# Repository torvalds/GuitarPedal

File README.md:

## Resurrected random guitar pedal project

This is a resurrected version of my old guitar pedal project: a digital
guitar pedal built around an RP2354A and a TI audio codec, with all the
effects done in software on a core of its own.

It went through a phase with a little OLED screen and a couple of rotary
encoders on it, and that's gone now.  Editing seventeen effects through a
128x128 screen and two knobs was never going to be pleasant, and I'm not
exactly known for my mad UI designing skillz, so the pedal itself is down
to one knob and one stomp switch and the deep editing happens somewhere
that already has a screen: there's a web app that talks to it over USB
MIDI from a browser.

So what's in here:

 - `Hardware` has the kicad files.
 - `Effects` has the seventeen effects, one file each.  They are up here
   rather than inside the firmware because three different things are
   built from them: the firmware, the test bench, and the web app's
   controls.
 - `Audio` has the DSP the effects are built out of - biquads, envelope
   followers, LFOs - and the audio loop itself.  The bench compiles the
   same files, so what gets measured is the pedal's own arithmetic.
 - `Firmware` is the rest of what runs on the pedal: USB, MIDI, scenes,
   the board pin maps.
 - `WebMIDI` is the web app that edits it.
 - `scripts` is what the build runs - the effect generator, the math
   tables, and the checks that refuse a firmware image doing something
   the audio core shouldn't.
 - `Validation` is the test suite.  Some of it runs on your machine and
   some of it wants a pedal plugged in.
 - `Documentation` remains a very optimistic name for a directory.

## Firmware

I've only ever built the firmware on Linux, but it *should* be perfectly
possible to build on MacOS or Windows too if you just figure out the
platform requirements. The project depends on the `pico-sdk` and
`tinyusb` libraries and on `picotool`, and has submodules for all three, so
they get built automatically, but the build tools your platform has to provide.

Regardless of platform, you'll need the basics:
 - git
 - make
 - python3
 - cmake
 - a C and C++ compiler for the machine you build on, because picotool
   and the SDK's PIO assembler are built from source too
 - pkg-config and the libusb-1.0 development files, for picotool
   (`libusb1-devel` on Fedora, `libusb-1.0-0-dev` on Debian)

and a 32-bit arm cross-build environment.  On Linux, that would be
something like
 - arm-none-eabi-binutils-cs
 - arm-none-eabi-gcc-cs
 - arm-none-eabi-gcc-cs-c++ (the SDK sets up C++ as well as C)
 - arm-none-eabi-newlib

On Fedora that whole list is

    dnf install git make python3 cmake gcc-c++ pkgconf-pkg-config \
        libusb1-devel arm-none-eabi-gcc-cs arm-none-eabi-gcc-cs-c++ \
        arm-none-eabi-newlib

The `ble` board also carries the nRF54 radio's firmware, which is a
Zephyr build of its own.  ``make -C nRF54 fetch`` sets that up once: a
python venv with west in it, the Nordic SDK, and Zephyr's ARM toolchain
in `~/zephyr-sdk-*`, about 7.5GB between them.  It also needs ninja
(`ninja-build` on Fedora).

There's more than one board this can be built for, and the build won't
guess.  You say which one this tree is about once, in
`board.local`, and it stays said - it's a file rather than a
cmake cache variable specifically so that blowing away `build/` doesn't
silently change your mind for you.  So:
```
	git clone https://github.com/torvalds/GuitarPedal.git
	cd GuitarPedal
	echo unified > board.local
	make prep
	make
```
`unified` is the current one-board pedal.  The other is `split`, which is
the older modular pair of boards.  If you forget this step the configure
will stop and tell you, which is the intended behaviour - a wrong board
should be an error you fix once, not a working build for hardware you
don't have.

That gets you `build/pedal-unified.uf2` (and `.elf`, and `.bin`).  Every
artifact is named for the board it's for, so there is deliberately no
`pedal.uf2` to grab by mistake.  You can build the other board without
changing what the tree is about - ``make split`` - or both with ``make
all-boards``.

To get the `.uf2` onto the pedal you need it in BOOTSEL mode, and there
are two ways.  If it's running and plugged in, send it MIDI CC 20 with
value 126 and it will reboot into BOOTSEL on its own:
```
	amidi -l                          # find which card the pedal is
	amidi -p hw:5,0 -S "B0 14 7E"     # ...and that 5 is mine, not yours
```
Otherwise, hold the knob in while you plug it in.  The rotary encoder's
switch doubles as BOOTSEL on this board - through a Schottky, so that
QSPI traffic can't fake pulling it low - and that's the route that still
works on a pedal too broken to enumerate.  The older boards had a proper
BOOTSEL button, but it was on the little MCU daughtercard, which is fine
on a bench and useless the moment the thing is screwed into a box.

Either way a USB mass storage device shows up and you copy the file to
it.

The build makes its own picotool, with USB support, so you can also skip
all that and just do ``make flash``, which builds and flashes the board in
`board.local`.
``make flash-split`` does the other one.

### Tools outside the tree

Two tools stay outside the tree, and each has a make target that
sets it up once per machine.  Both say what they are missing, and
running either again is safe.

``make probe-rs`` builds probe-rs, which programs and debugs the nRF54
radio through the pedal, from `~/src/probe-rs` into `~/bin/probe-rs`.
It needs cargo and the libudev development files (`systemd-devel` on
Fedora).

``make build123d`` makes a python venv in `~/.build123d` for the
3D-printed case in `Hardware/Models`, and two commands in `~/bin` that
use it: ``build123d Compact.py`` runs the model, and ``ocp-viewer`` is
the viewer it draws in, at http://localhost:3939.

### Talking to the pedal without root

picotool and probe-rs open the pedal's USB device directly, and without
a udev rule only root can.  This is `/etc/udev/rules.d/99-pedal.rules`:

    ATTR{idVendor}=="2e8a", MODE="0660", GROUP="dialout"
    ATTR{idVendor}=="ffff", ATTR{idProduct}=="0003", MODE="0660", GROUP="dialout"

The first line covers anything with Raspberry Pi's vendor id, which is
how a board in BOOTSEL shows up; the second is the running pedal, whose
CMSIS-DAP interface is what probe-rs uses for the radio.  You have to be
in the `dialout` group, and ``udevadm control --reload`` as root plus a
replug picks the rule up.  USB audio and MIDI need no rule.

The pedal's debug console is `/dev/ttyACM0`, which needs a kernel with
`CONFIG_USB_ACM`.  Every distribution kernel has it; a kernel you
configured yourself may not.

### Testing

`Validation` has the test suite, and it's split by what it needs.

``make check`` needs gcc and numpy (`python3-numpy`), plus node if
you want the web app's tests too; without node those are skipped.  The
bench scripts that talk to a pedal want more: alsa-utils, ffmpeg, scipy
and matplotlib, ngspice for the circuit comparisons, and dbus-python and
PyGObject for Bluetooth MIDI.  On Fedora,

    dnf install python3-numpy nodejs alsa-utils ffmpeg-free psmisc \
        python3-scipy python3-matplotlib ngspice python3-dbus python3-gobject

``make check`` runs the part that needs no hardware at all: the MIDI
packetiser, whether the web app still loads and still draws the right
conclusions, and a sweep that asks every biquad in the pedal where it
actually landed.  ``make check-biquad`` is that last one on its own, and
``make check-effects`` puts signals through the effects themselves.

That last one works because of `Validation/bench`, which builds the
pedal's actual audio core - the same `single_sample()`, the same effect
headers, the same compiler flags - as a program on your machine that
takes float samples on stdin and hands them back on stdout.  It is not a
model of the signal path.  It's the signal path, with the two register
blocks the audio core touches replaced by ordinary memory.

``make check-analysis`` is the other host-only one, and it is what keeps
the per-effect pages under `Documentation/effects` honest: every curve on
those pages is a measurement, and this re-measures and says when one has
stopped being true.  It is separate from ``check`` because it re-runs
every sweep on every page, which is slow.

Then there are the ones that want hardware: ``make check-hw`` with a
signal generator, ``make check-analog`` with a patch cable from the
pedal's output back to its own input, ``make check-bench`` to ask whether
a real board agrees with the host build, ``make check-hwtone`` to sweep
the tone stack the codec runs in its own biquads, and ``make check-loop``
if you have two pedals to patch into each other.

### Checking generated metadata

After generating metadata, check existing outputs without changing them:

```sh
python3 scripts/gen_effects.py --check Effects/ build/effect_map.h WebMIDI/effects.js Documentation/MIDI_CC_MAP.md
```

Use the output paths from your build if they differ. This checks the three
named files and `midi_schema.h` beside the C header. Exit status is 0 when
current, 1 for missing or stale output, and 2 for an input or I/O error.
Missing/stale files are listed with a regeneration command. Ordinary
generation without `--check` remains the way to create or refresh them.
Run the hardware-free regression tests with
`make -C Validation test-generated-metadata`; they also run under
`make -C Validation check`.

## Hardware

The kicad design files (and some supporting infrastructure, like the 3D
printed insert and the enclosure drill rules) are in the ``Hardware``
subdirectory.

These days it's just the one board.  `Hardware/usb-stomp` has the RP2354A
and the TI TAC5242 codec sitting directly on it, and that's the whole
pedal: no cable, no daughtercards, no connectors in between.

What's on it:

 - a 1/4" input jack and a 1/4" output jack
 - a third 1/4" jack for an expression pedal or a remote stomp switch
 - MIDI in and out, on 3.5mm "Type A" TRS jacks (out through a 5V
   buffer, in through an optocoupler, like MIDI has always wanted)
 - USB-C, and the usual 9V guitar pedal power jack
 - one rotary encoder with a switch under it, and one stomp switch
 - three addressable WS2812B LEDs

The MIDI jacks and the expression jack are the genuinely new things.  The
older boards had nowhere to put them - the expression jack in particular
wants two ADC pins, and those are exactly the pins the old MCU board was
spending on hardware MIDI, so it could not have existed there at all.

Fair warning on that expression jack, though: the hardware is done and
the firmware can read it, but only when the host asks it to over SysEx.
Right now it's a probe for figuring out what people actually plug in
there - expression pedals don't even agree on which contact is the wiper
- and nothing is wired up to *do* anything with the result yet.

### How it used to be

It used to be modular, and those board files are all still here.  There
were two little daughtercards for the "core" hardware - the RP2354
microcontroller (`Hardware/rp2354`) and the TI TAC5112 codec
(`Hardware/codec`) - plus a board for the audio and 9V DC power jacks
(`Hardware/audio-jacks`), and a main board (`Hardware/pedal-board`) for
the pedal IO: i2c connector for the screen, USB-C programming port,
rotary encoders, pin header for stomp switches.  The two halves were
joined by a 12P 0.5mm FFC cable carrying power and data lines (i2c for
control, i2s for audio).

That was mostly so I could try out different form factors.  It let me lay
the two halves out independently, and it was flexible enough to cram a
125B enclosure full of jacks, rotaries and the screen all in one top
area.  There was also a worry about noise isolation, which in the end
never had to be tested.

I used the nice HiRose BM28 series connectors on the modular boards.
They are absolutely tiny, which makes for a great board footprint but
admittedly also makes for a slightly more complicated board due to the
tiny 0.35mm pitch.  I'm not a fan of the traditional pin headers simply
because they make it so hard to do compact form factors.

Those boards are finished and they still work - the firmware builds for
them, and they're still useful for testing.  But what this section used
to say was that if you know what you want, you should just put the codec
directly on the audio jack board and the rp2354 on the IO board.  Which,
yes.  That's the board above.

### Images

The bare `usb-stomp` board, powered up.

## Basic UI

There's no screen.  The pedal has one knob, one footswitch and three
LEDs, and everything else happens in a browser.

### On the pedal

Out of the box the footswitch is bypass - tap for in-circuit or not, hold
it for the tuner - and the knob is the master volume, with either kind of
press on it putting the volume back where it started.  That last one
sounds trivial and isn't: it's the way back when you can't see anything.

But none of that is compiled in.  There are five gestures - turn the
knob, tap it, hold it, tap the switch, hold the switch - and what each
one means is a table the pedal looks up and the app writes.  You can
point the knob at any parameter of any effect, or make a single press
take one effect's mix up while it takes another's down.  A pedal with no
screen can't tell you what its knob is for, so that has to be settable
from something that can.

The three LEDs, left to right: something is wrong (red for clipping,
amber for dropped samples), in circuit or bypassed, and the chain is
busy - where "busy" means whatever the effect thinks it means, so the
gate lights it while it's gating and the compressor while it's
compressing.

### In the browser

`WebMIDI` is a static web page that talks to the pedal over USB
MIDI.  There's nothing to install and it runs off a phone.

It also talks to the pedal over Bluetooth MIDI.  On Linux, Chrome only
offers Bluetooth to a page with
`chrome://flags/#enable-experimental-web-platform-features` turned on;
USB needs nothing.

It doesn't know what the effects are.  It asks.  The pedal describes
every effect it has - every pot, the ranges, the units, the hover text -
and the app builds itself out of that, so it can't drift out of step with
the firmware, and adding an effect to the pedal makes it show up in the
app without touching the app.

What you actually do there is *route*.  There are seventeen effects and
none of them are in your signal path until you say so: routing picks
which ones run, and in what order, and the order is yours, because a
boost in front of a delay is a different pedal from a delay in front of a
boost.  Whatever you don't route costs nothing.

Pots are mostly just numbers, except where they aren't - the tone stacks,
the parametric EQ and the cab sim draw their actual frequency response,
so you can see the curve instead of inferring it from three knob
positions.

A tone stack with a 10dB mid bump at 810Hz and a tape echo behind it, and
the fifteen effects that aren't routed sitting at the bottom waiting to
be.  The faint grey line is the phase response.

Eight scenes fit in the pedal's own flash.  A scene is a routing plus
everything set inside it, and a MIDI program change recalls one, which is
half of what those MIDI jacks are for: a cheap footswitch can step
between scenes with no computer in sight.

## Audio effects

Nineteen of them, plus five that are always there and can't be
unrouted: the **Signal Chain** at the front, which is the input trim, the
noise gate and the master volume
([measured](Documentation/effects/signal-chain.md)), and behind them the
**Settings**, which is whether the input jack is carrying one channel or
two, the MIDI channel, LED brightness and what the tuner is tuning to,
the **USB Audio**, which is what crosses the wire in each direction, the
**Bluetooth Audio**, which is where audio from a phone joins, how loud it
is and what goes back, on a board with a radio, and the **Expression Jack**, which is what
is plugged into it and where that thing's travel ends.

They're listed in the order they run in by default.  This is an overview
and not documentation - the app is the reference, because it gets the
ranges, the units and the hover text from the pedal itself rather than
from anything I typed here.

 - **Hum Filter** - removes the hum single coils and noisy power put on
   the guitar, cutting only the hum's own frequencies, so a clean supply
   gets no cuts at all.  Switching it on the first time, or moving the
   target, listens for a few seconds with the sound left on, so you hear
   the hum go: keep the strings quiet while it does.  It runs ahead of
   the noise gate.  It does not reach the high buzz some USB chargers
   add, and a power bank is quieter there anyway.
 - **Tone** - bass, mid and treble, with the corner frequencies
   adjustable and the mid's Q as well.  There are two of them, so one
   can go in front of a distortion and one behind it.
 - **Analog In Tone** and **Analog Out Tone** - the same three bands
   again, running in the codec's own biquads rather than in the chain.
   They cost the audio core nothing, and they keep the two channels
   apart where Tone folds them together.  Routed like anything
   else, but drawn at the ends of the chain because that is where they
   are: analog is the operative word, and they sit outside everything
   USB audio can reach, so a Dry capture has already been through the
   input one and a Wet capture has not yet been through the output one.
   They need a board whose codec answers on i2c.
 - **Preamp** - a two-stage 12AX7 model, class-A biased with the
   asymmetry left in, and a JFET stage after it.
 - **Compressor** - level, ratio, attack, release, and a boost, so it
   can also just be a clean boost when that's what you want.  The
   threshold reaches low enough to work on a quiet pickup with nothing
   in front of it.  [Measured](Documentation/effects/compressor.md).
 - **Auto-Wah** - an envelope filter that sweeps a resonant filter with
   the guitar's pick dynamics, by Jacky Mpoka.  Lowpass mode preserves low-end body while
   sweeping harmonics (Mu-Tron III style); Bandpass mode isolates the
   resonant peak for classic vocal wah (Crybaby style).  Sweeps up for
   funk quack or down for synth sweeps.
 - **Boost**, with distortion.  I like this one.  Others may not.  Set
   the boost stupidly high and the level low, and instead of clipping at
   the level the signal *folds* back down, which gives you harmonics
   that a soft or hard clipper doesn't.
 - **Klonlike** - the obvious model: 18V charge pump for headroom,
   germanium diodes, and the clean/dirty blend that tracks the gain
   knob.  Originally by Bryan Leavelle.
   [Measured](Documentation/effects/klon.md).
 - **Rat Sketch** - a ProCo RAT, from the Aion FX Helios clone.  One
   op-amp with up to 67dB and several decibels an octave of treble
   emphasis inside the feedback, then diodes to ground, then the one
   backwards Filter knob.  Three clipping modes, because the pedal has
   three.  The op-amp saturates inside its own loop and the diodes are
   solved rather than approximated, which is where its second harmonic
   comes from.  [Measured](Documentation/effects/rat.md).
 - **Phaser**, **Flanger** and **Vibrato** - the modulation three.  All
   simple, all a delay line and an LFO wearing different hats.
 - **Tape Echo** - the Echo King from Cleveland Music Co, a model of the
   Maestro Echoplex tape delays, converted from the Hothouse examples.
   All credit to Ricky Sheaves, and blame me for the conversion.
 - **Reverb** - comb filters into allpasses, the traditional way.
   [Measured](Documentation/effects/reverb.md).
 - **Pitch** - not the clever FFT kind.  It walks a delay line faster or
   slower than real time in two phases, crossfaded with a sine so the
   wrap doesn't click.  So it shifts *and* delays, and it feeds back into
   itself, which makes it a short echo that shifts again on every repeat.
   Most natural an octave up, but it does fractions.
 - **Tremolo** - amplitude modulation, several shapes.
 - **Parametric EQ** - five bands, two shelves and three peaks, every one
   of them tunable across the whole range.
 - **Frenchie Amp** - a small amp: triode, tone stack, power amp.
 - **Test Tone** - sine, triangle, saw or noise at a known level and
   frequency.  It replaces the input rather than adding to it, which is
   what lets the pedal measure itself.
 - **Cabinet** - a speaker cone as a moving mass rather than as a filter,
   integrated at the sample rate.  Pick one of five cabinets and it knows
   the rest of itself; the knobs are how hard the amp drives it, how much
   the amp lets its resonance bloom, and where the mic is pointed.

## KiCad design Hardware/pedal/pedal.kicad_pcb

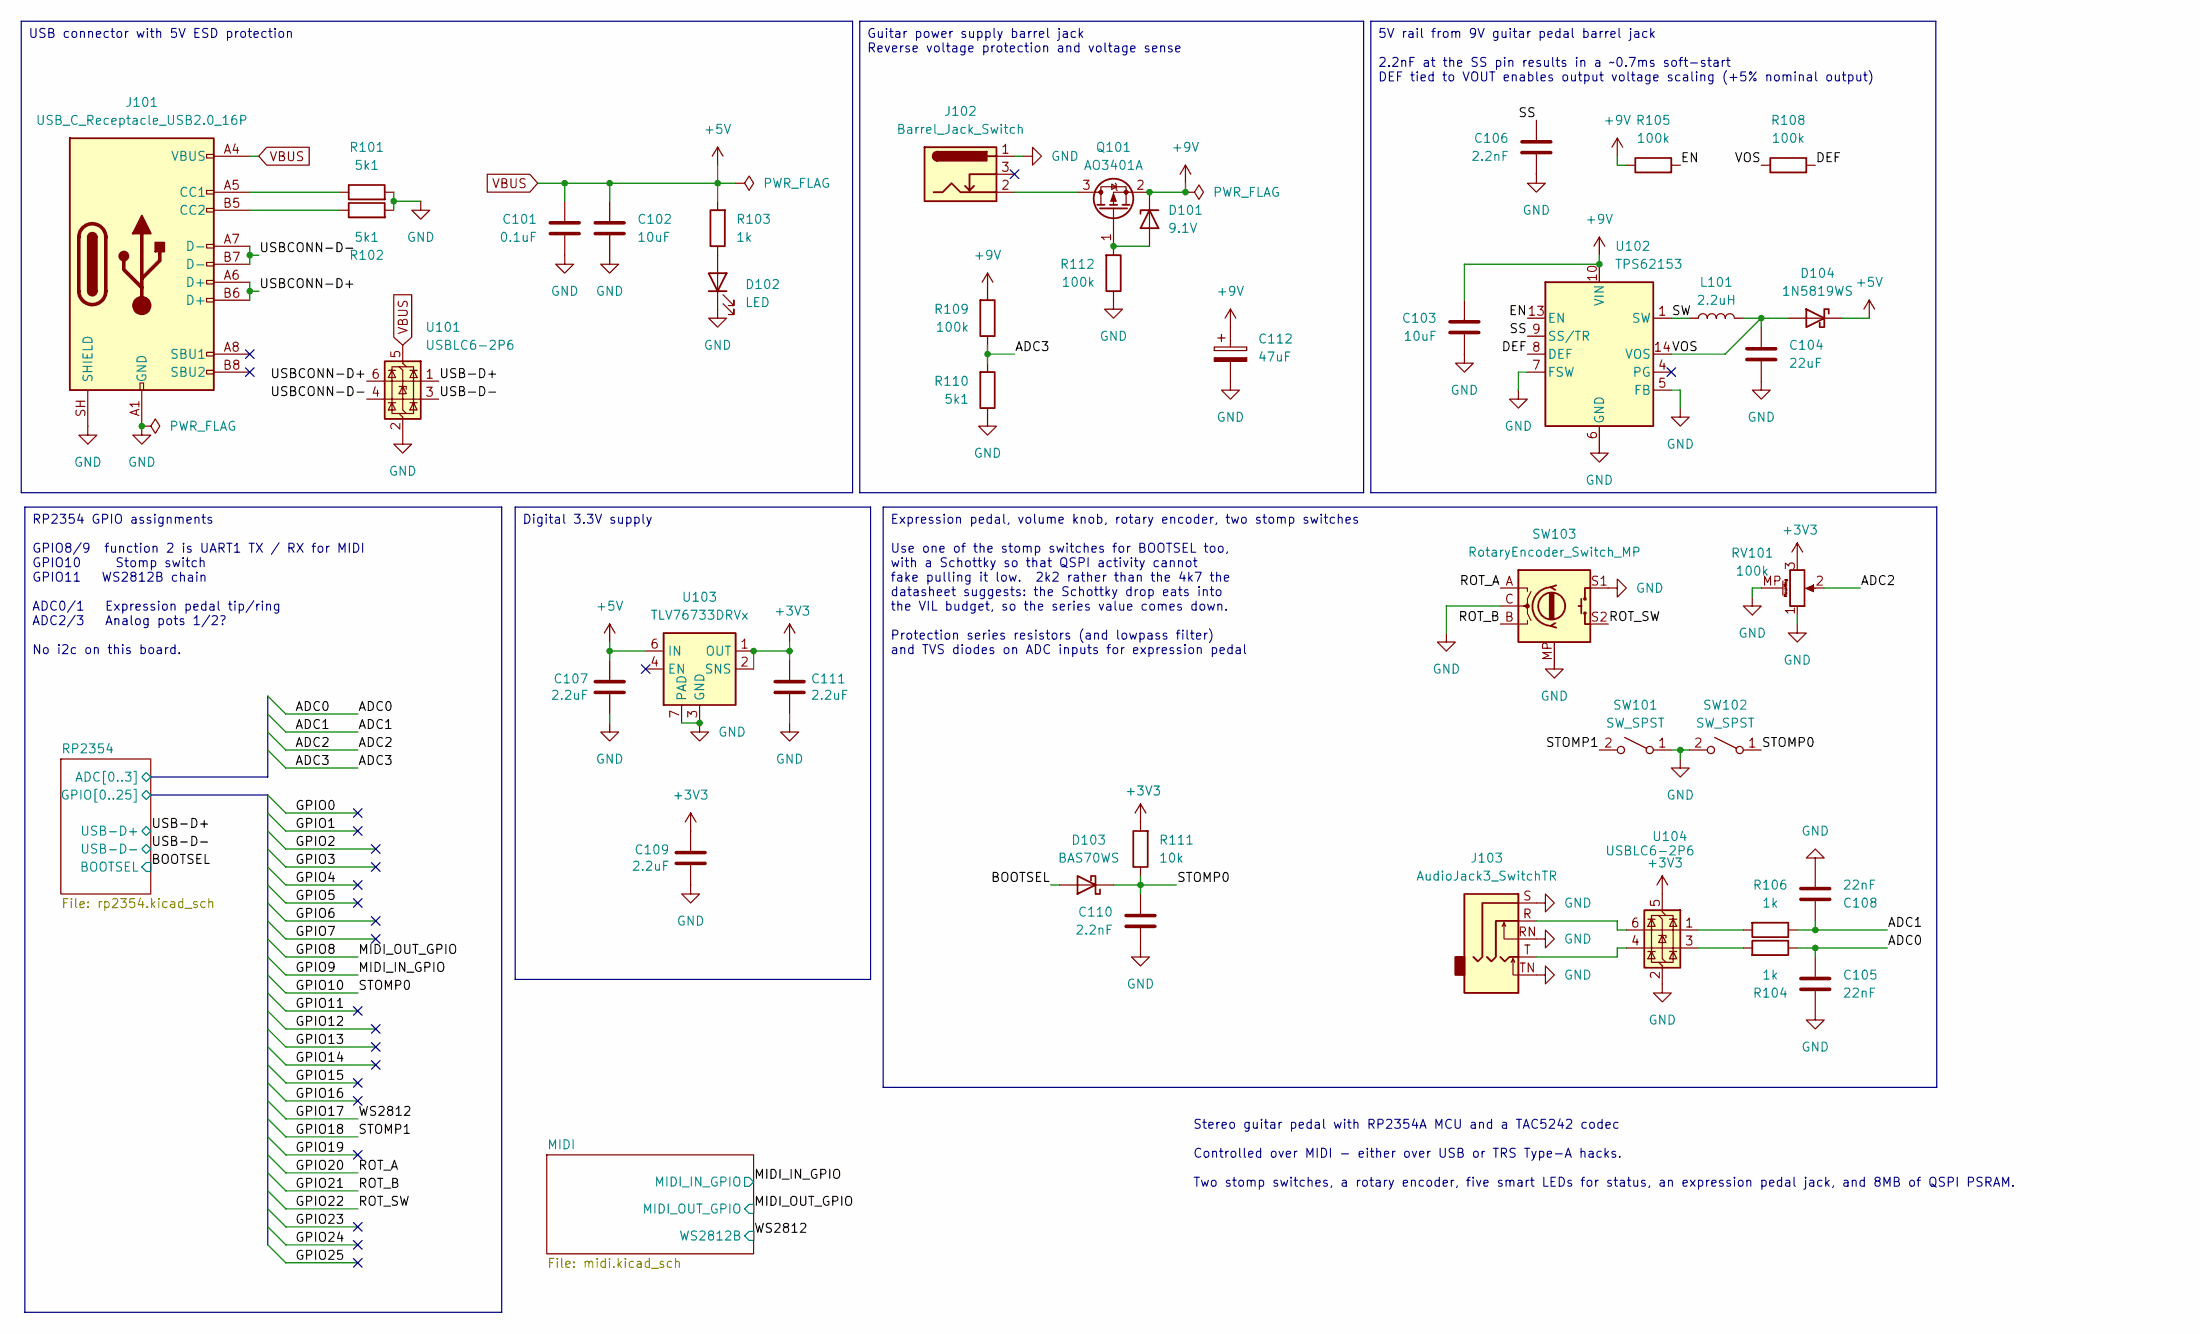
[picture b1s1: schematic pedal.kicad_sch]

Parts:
C101: 0.1uF; C_0402_1005Metric; MANUFACTURER_PART_NUMBER CL05B104KO5NNNC; LCSC PN C1525
C102, C103: 10uF; C_0603_1608Metric; MANUFACTURER_PART_NUMBER GRM188R61E106MA73D; LCSC PN C91606
C104: 22uF; C_1210_3225Metric; MANUFACTURER_PART_NUMBER CL32B226KAJNNNE; LCSC PN C309062
C105, C108: 22nF; C_0402_1005Metric; MANUFACTURER_PART_NUMBER 0402B223K500NT; LCSC PN C1532
C106, C110: 2.2nF; C_0402_1005Metric; MANUFACTURER_PART_NUMBER GRM1555C1H222GA01D; LCSC PN C2987940
C107, C109, C111: 2.2uF; C_0603_1608Metric; MANUFACTURER_PART_NUMBER GRM188Z71E225KE43D; LCSC PN C415535
C112: 47uF; CP_Elec_6.3x5.9; MANUFACTURER_PART_NUMBER EEHZA1V470P; LCSC PN C178639
D101: 9.1V; D_SOD-323; MANUFACTURER_PART_NUMBER BZT52C9V1S; LCSC PN C19077445
D102: LED; LED_0402_1005Metric; MANUFACTURER_PART_NUMBER LTST-C281KGKT; LCSC PN C160479
D103: BAS70WS; D_SOD-323; MANUFACTURER_PART_NUMBER BAS70WS; LCSC PN C7502716
D104: 1N5819WS; D_SOD-323; MANUFACTURER_PART_NUMBER 1N5819WS; LCSC PN C191023
J101: USB_C_Receptacle_USB2.0_16P; USB_C_Receptacle_GCT_USB4105-xx-A_16P_TopMnt_Horizontal; MANUFACTURER_PART_NUMBER GT-USB-7010C; LCSC PN C2843967
J102: Barrel_Jack_Switch; Wurth WR-DC 2.1mm Power Jack
J103: AudioJack3_SwitchTR; NRJ6HM-1-PRE
L101: 2.2uH; L_0806; MANUFACTURER_PART_NUMBER DFE201612E-2R2M=P2; LCSC PN C337893
Q101: AO3401A; SOT-23; MANUFACTURER_PART_NUMBER AO3401A; LCSC PN C15127
R101, R102, R110: 5k1; R_0402_1005Metric; MANUFACTURER_PART_NUMBER 0402WGF5101TCE; LCSC PN C25905
R103, R104, R106: 1k; R_0402_1005Metric; MANUFACTURER_PART_NUMBER RT0402FRE071KL; LCSC PN C136974
R105, R108, R109, R112: 100k; R_0402_1005Metric; MANUFACTURER_PART_NUMBER 0402WGF1003TCE; LCSC PN C25741
R111: 10k; R_0402_1005Metric; MANUFACTURER_PART_NUMBER 0402WGF1002TCE; LCSC PN C25744
RV101: 100k; Potentiometer_9mm_MP_Low_profile
SW101, SW102: SW_SPST; Daier PBS-24B-4
SW103: RotaryEncoder_Switch_MP; RotaryEncoder_EC11-Switch_Vertical_H20mm
U101, U104: USBLC6-2P6; SOT-666; MANUFACTURER_PART_NUMBER USBLC6-2P6; LCSC PN C15999
U102: TPS62153; VQFN-16-1EP_3x3mm_P0.5mm_EP1.68x1.68mm_ThermalVias; MANUFACTURER_PART_NUMBER TPS62153RGTR; LCSC PN C477927
U103: TLV76733DRVx; WSON-6-1EP_2x2mm_P0.65mm_EP1x1.6mm; MANUFACTURER_PART_NUMBER TLV76733DRVR; LCSC PN C2848334

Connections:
+3V3: C109.1, C111.1, R111.2, RV101.3, U103.1 (OUT), U103.2 (SNS), U104.5 (VBUS); also elsewhere on the board
+9V: C103.1, C112.1, D101.1 (K), Q101.2 (S), R105.1, R109.2, U102.10 (VIN), U102.11 (VIN), U102.12 (VIN)
/BOOTSEL: D103.2 (A); also elsewhere on the board
/DEF: R108.2, U102.8 (DEF)
/EN: R105.2, U102.13 (EN)
/RP2354/ADC0: C105.1, R104.1; also elsewhere on the board
/RP2354/ADC1: C108.1, R106.1; also elsewhere on the board
/RP2354/ADC2: RV101.2; also elsewhere on the board
/RP2354/ADC3: R109.1, R110.2; also elsewhere on the board
/RP2354/GPIO10: C110.2, D103.1 (K), R111.1, SW102.1 (A); also elsewhere on the board
/RP2354/GPIO18: SW101.2 (B); also elsewhere on the board
/RP2354/GPIO20: SW103.A; also elsewhere on the board
/RP2354/GPIO21: SW103.B; also elsewhere on the board
/RP2354/GPIO22: SW103.S2; also elsewhere on the board
/SS: C106.2, U102.9 (SS/TR)
/SW: L101.1, U102.1 (SW), U102.2 (SW), U102.3 (SW)
/USB-D+: U101.1 (I/O1); also elsewhere on the board
/USB-D-: U101.3 (I/O2); also elsewhere on the board
/USBCONN-D+: J101.A6 (D+), J101.B6 (D+), U101.6 (I/O1)
/USBCONN-D-: J101.A7 (D-), J101.B7 (D-), U101.4 (I/O2)
/VOS: C104.1, D104.2 (A), L101.2, R108.1, U102.14 (VOS)
GND: C101.1, C102.2, C103.2, C104.2, C105.2, C106.1, C107.2, C108.2, C109.2, C110.1, C111.2, C112.2, D102.1 (K), J101.A1 (GND), J101.A12 (GND), J101.B1 (GND), J101.B12 (GND), J101.SH (SHIELD), J102.1, J103.RN, J103.S, J103.TN, R101.2, R102.2, R110.1, R112.1, RV101.1, RV101.MP (MountPin), SW101.1 (A), SW102.2 (B), SW103.C, SW103.MP, SW103.S1, U101.2 (GND), U102.5 (FB), U102.6 (GND), U102.7 (FSW), U102.15 (GND), U102.16 (GND), U102.17 (GND), U103.3 (GND), U103.5 (GND), U103.7 (PAD), U104.2 (GND); also elsewhere on the board
unnamed: D101.2 (A), Q101.1 (G), R112.2
unnamed: D102.2 (A), R103.1
unnamed: J101.A5 (CC1), R101.1
unnamed: J101.B5 (CC2), R102.1
unnamed: J103.R, U104.6 (I/O1)
unnamed: J103.T, U104.4 (I/O2)
unnamed: J102.2, Q101.3 (D)
unnamed: R104.2, U104.3 (I/O2)
unnamed: R106.2, U104.1 (I/O1)
VBUS: C101.2, C102.1, C107.1, D104.1 (K), J101.A4 (VBUS), J101.A9 (VBUS), J101.B4 (VBUS), J101.B9 (VBUS), R103.2, U101.5 (VBUS), U103.6 (IN); also elsewhere on the board

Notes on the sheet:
Stereo guitar pedal with RP2354A MCU and a TAC5242 codec Controlled over MIDI - either over USB or TRS Type-A hacks. Two stomp switches, a rotary encoder, five smart LEDs for status, an expression pedal jack, and 8MB of QSPI PSRAM.
Expression pedal, volume knob, rotary encoder, two stomp switches Use one of the stomp switches for BOOTSEL too, with a Schottky so that QSPI activity cannot fake pulling it low. 2k2 rather than the 4k7 the datasheet suggests: the Schottky drop eats into the VIL budget, so the series value comes do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
5V rail from 9V guitar pedal barrel jack 2.2nF at the SS pin results in a ~0.7ms soft-start DEF tied to VOUT enables output voltage scaling (+5% nominal output)
RP2354 GPIO assignments GPIO8/9 function 2 is UART1 TX / RX for MIDI GPIO10 Stomp switch GPIO11 WS2812B chain ADC0/1 Expression pedal tip/ring ADC2/3 Analog pots 1/2? No i2c on this board.
Digital 3.3V supply
Guitar power supply barrel jack Reverse voltage protection and voltage sense
USB connector with 5V ESD protection

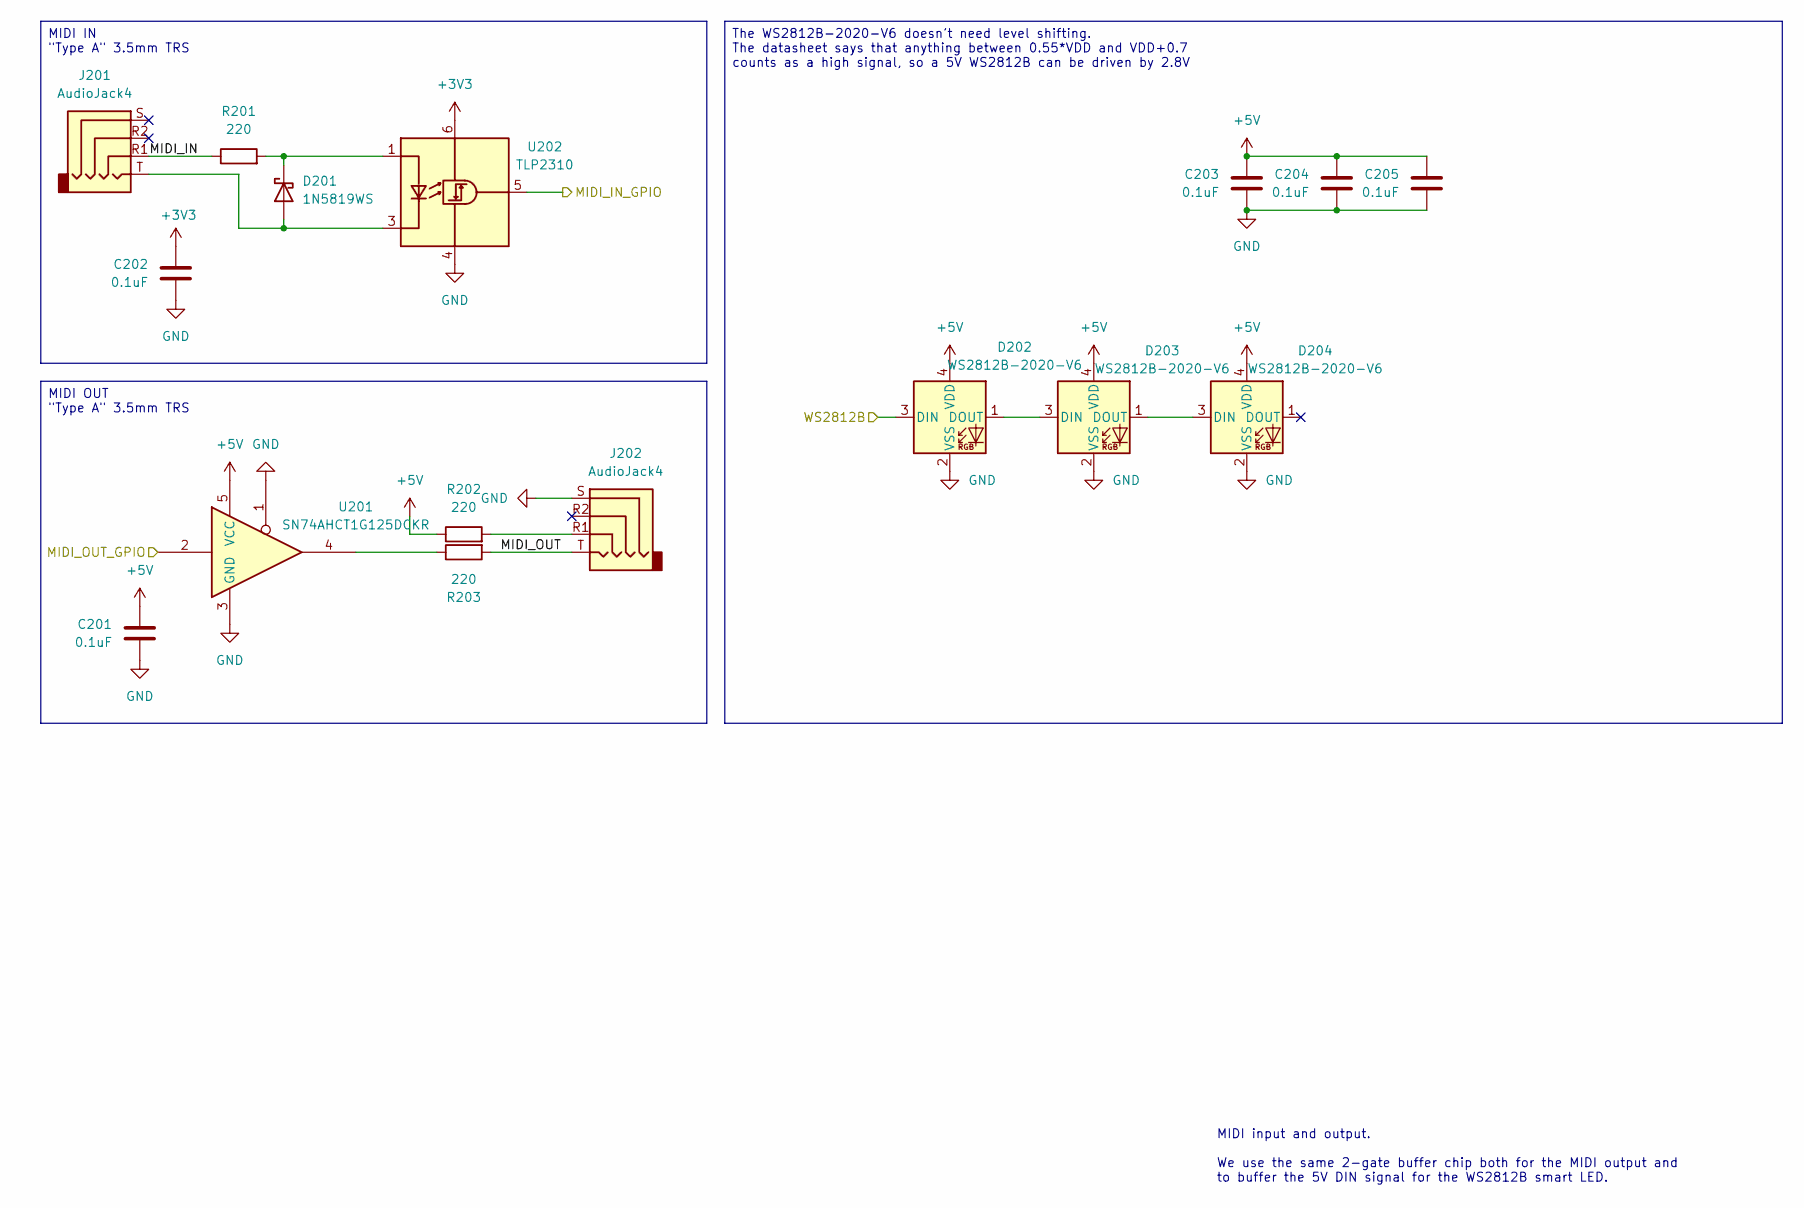
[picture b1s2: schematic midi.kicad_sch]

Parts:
C201, C202, C203, C204, C205: 0.1uF; C_0402_1005Metric; MANUFACTURER_PART_NUMBER CL05B104KO5NNNC; LCSC PN C1525
D201: 1N5819WS; D_SOD-323; MANUFACTURER_PART_NUMBER 1N5819WS; LCSC PN C191023
D202, D203, D204: WS2812B-2020-V6; LED_WS2812B-2020_PLCC4_2.0x2.0mm; MANUFACTURER_PART_NUMBER WS2812B-2020-V6; LCSC PN C52917434
J201, J202: AudioJack4; PJ-320D; MANUFACTURER_PART_NUMBER PJ-320D; LCSC PN C431535
R201, R202, R203: 220; R_0402_1005Metric; MANUFACTURER_PART_NUMBER 0402WGF2200TCE; LCSC PN C25091
U201: SN74AHCT1G125DCKR; SOT-353_SC-70-5; MANUFACTURER_PART_NUMBER SN74AHCT1G125DCKR; LCSC PN C350557
U202: TLP2310; SO-5-6_4.55x3.7mm_P1.27mm; MANUFACTURER_PART_NUMBER TLP2310; LCSC PN C7473281

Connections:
+3V3: C202.2, U202.6 (VDD); also elsewhere on the board
/MIDI/MIDI_IN: J201.R1, R201.1
/MIDI/MIDI_OUT: J202.T, R203.2
/RP2354/GPIO8: U201.2; also elsewhere on the board
/RP2354/GPIO9: U202.5 (VO); also elsewhere on the board
/RP2354/GPIO17: D202.3 (DIN); also elsewhere on the board
GND: C201.1, C202.1, C203.1, C204.1, C205.1, D202.2 (VSS), D203.2 (VSS), D204.2 (VSS), J202.S, U201.1, U201.3 (GND), U202.4 (GND); also elsewhere on the board
unnamed: D201.2 (A), J201.T, U202.3 (K)
unnamed: D201.1 (K), R201.2, U202.1 (A)
unnamed: D202.1 (DOUT), D203.3 (DIN)
unnamed: D203.1 (DOUT), D204.3 (DIN)
unnamed: J202.R1, R202.2
unnamed: R203.1, U201.4
VBUS: C201.2, C203.2, C204.2, C205.2, D202.4 (VDD), D203.4 (VDD), D204.4 (VDD), R202.1, U201.5 (VCC); also elsewhere on the board

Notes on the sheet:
MIDI input and output. We use the same 2-gate buffer chip both for the MIDI output and to buffer the 5V DIN signal for the WS2812B smart LED.
MIDI IN "Type A" 3.5mm TRS
MIDI OUT "Type A" 3.5mm TRS
The WS2812B-2020-V6 doesn't need level shifting. The datasheet says that anything between 0.55*VDD and VDD+0.7 counts as a high signal, so a 5V WS2812B can be driven by 2.8V

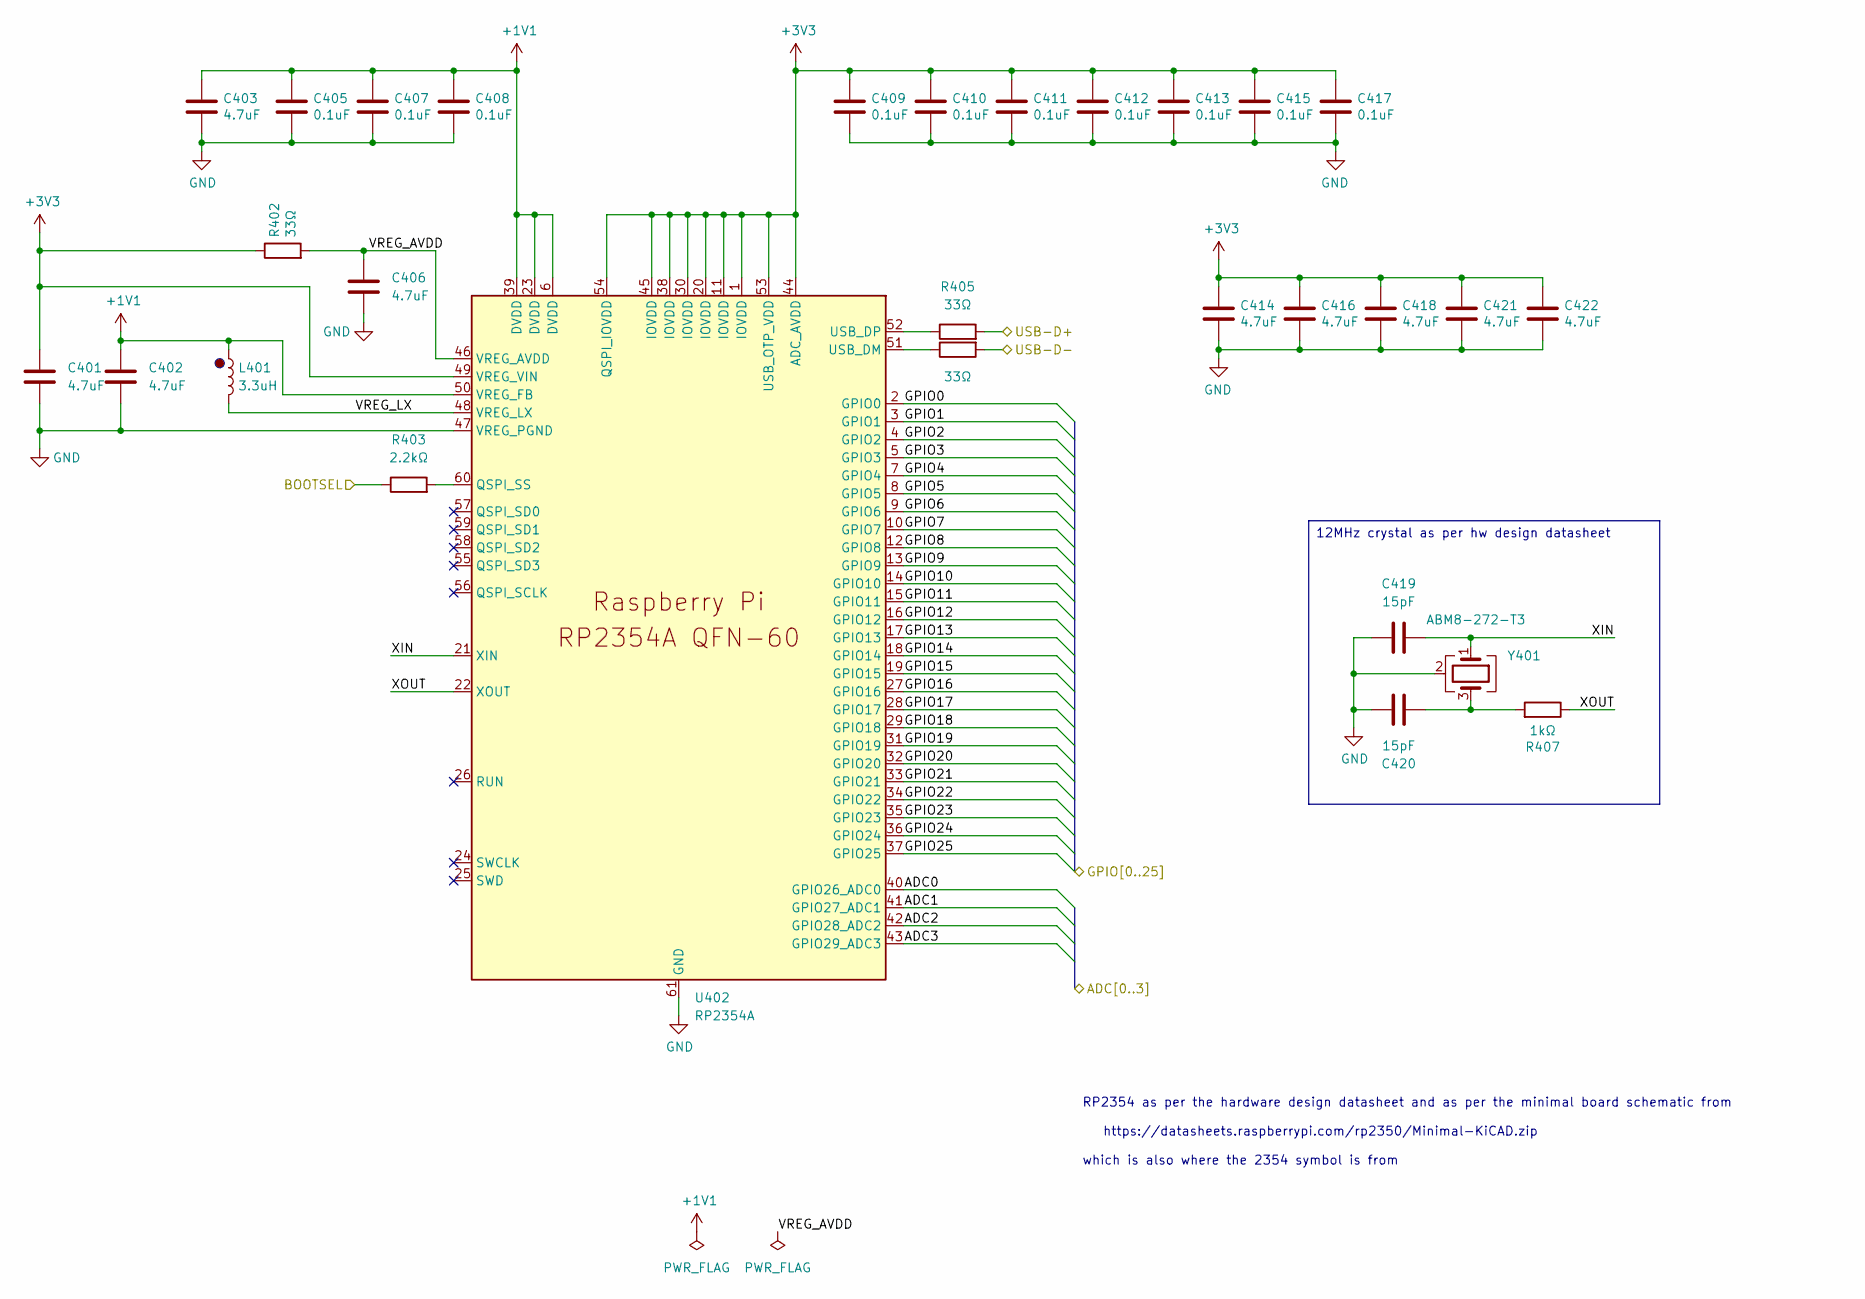
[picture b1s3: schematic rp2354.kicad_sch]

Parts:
C401, C402, C403, C406, C414, C416, C418, C421, C422: 4.7uF; C_0402_1005Metric; MANUFACTURER_PART_NUMBER GRM155R61E475ME15D; LCSC PN C2858031
C405, C407, C408, C409, C410, C411, C412, C413, C415, C417: 0.1uF; C_0402_1005Metric; MANUFACTURER_PART_NUMBER CL05B104KO5NNNC; LCSC PN C1525
C419, C420: 15pF; C_0402_1005Metric; MANUFACTURER_PART_NUMBER GRM1555C1H150JA01D; LCSC PN C76950
L401: 3.3uH; AOTA-B2016; MANUFACTURER_PART_NUMBER AOTA-B201610S3R3-101-T; LCSC PN C42411119
R402, R405, R406: 33Ω; R_0402_1005Metric; MANUFACTURER_PART_NUMBER 0402WGF330JTCE; LCSC PN C25105
R403: 2.2kΩ; R_0402_1005Metric; MANUFACTURER_PART_NUMBER 0402WGF2201TCE; LCSC PN C25879
R407: 1kΩ; R_0402_1005Metric; MANUFACTURER_PART_NUMBER 0402WGF1001TCE; LCSC PN C11702
U402: RP2354A; QFN-60-1EP_7x7mm_P0.4mm_EP3.4x3.4mm_ThermalVias; MANUFACTURER_PART_NUMBER RP2354A; LCSC PN C41378174
Y401: ABM8-272-T3; Crystal_SMD_3225-4Pin_3.2x2.5mm; MANUFACTURER_PART_NUMBER ABM8-272-T3; LCSC PN C20625731

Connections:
+1V1: C402.1, C403.1, C405.1, C407.1, C408.1, L401.1, U402.6 (DVDD), U402.23 (DVDD), U402.39 (DVDD), U402.50 (VREG_FB)
+3V3: C401.1, C409.1, C410.1, C411.1, C412.1, C413.1, C414.1, C415.1, C416.1, C417.1, C418.1, C421.1, C422.1, R402.1, U402.1 (IOVDD), U402.11 (IOVDD), U402.20 (IOVDD), U402.30 (IOVDD), U402.38 (IOVDD), U402.44 (ADC_AVDD), U402.45 (IOVDD), U402.49 (VREG_VIN), U402.53 (USB_OTP_VDD), U402.54 (QSPI_IOVDD); also elsewhere on the board
/BOOTSEL: R403.1; also elsewhere on the board
/RP2354/ADC0: U402.40 (GPIO26_ADC0); also elsewhere on the board
/RP2354/ADC1: U402.41 (GPIO27_ADC1); also elsewhere on the board
/RP2354/ADC2: U402.42 (GPIO28_ADC2); also elsewhere on the board
/RP2354/ADC3: U402.43 (GPIO29_ADC3); also elsewhere on the board
/RP2354/GPIO0: U402.2 (GPIO0)
/RP2354/GPIO1: U402.3 (GPIO1)
/RP2354/GPIO2: U402.4 (GPIO2)
/RP2354/GPIO3: U402.5 (GPIO3)
/RP2354/GPIO4: U402.7 (GPIO4)
/RP2354/GPIO5: U402.8 (GPIO5)
/RP2354/GPIO6: U402.9 (GPIO6)
/RP2354/GPIO7: U402.10 (GPIO7)
/RP2354/GPIO8: U402.12 (GPIO8); also elsewhere on the board
/RP2354/GPIO9: U402.13 (GPIO9); also elsewhere on the board
/RP2354/GPIO10: U402.14 (GPIO10); also elsewhere on the board
/RP2354/GPIO11: U402.15 (GPIO11)
/RP2354/GPIO12: U402.16 (GPIO12)
/RP2354/GPIO13: U402.17 (GPIO13)
/RP2354/GPIO14: U402.18 (GPIO14)
/RP2354/GPIO15: U402.19 (GPIO15)
/RP2354/GPIO16: U402.27 (GPIO16)
/RP2354/GPIO17: U402.28 (GPIO17); also elsewhere on the board
/RP2354/GPIO18: U402.29 (GPIO18); also elsewhere on the board
/RP2354/GPIO19: U402.31 (GPIO19)
/RP2354/GPIO20: U402.32 (GPIO20); also elsewhere on the board
/RP2354/GPIO21: U402.33 (GPIO21); also elsewhere on the board
/RP2354/GPIO22: U402.34 (GPIO22); also elsewhere on the board
/RP2354/GPIO23: U402.35 (GPIO23)
/RP2354/GPIO24: U402.36 (GPIO24)
/RP2354/GPIO25: U402.37 (GPIO25)
/RP2354/VREG_AVDD: C406.1, R402.2, U402.46 (VREG_AVDD)
/RP2354/VREG_LX: L401.2, U402.48 (VREG_LX)
/RP2354/XIN: C419.1, U402.21 (XIN), Y401.1
/RP2354/XOUT: R407.1, U402.22 (XOUT)
/USB-D+: R405.2; also elsewhere on the board
/USB-D-: R406.2; also elsewhere on the board
GND: C401.2, C402.2, C403.2, C405.2, C406.2, C407.2, C408.2, C409.2, C410.2, C411.2, C412.2, C413.2, C414.2, C415.2, C416.2, C417.2, C418.2, C419.2, C420.2, C421.2, C422.2, U402.47 (VREG_PGND), U402.61 (GND), Y401.2 (G), Y401.4 (G); also elsewhere on the board
unnamed: C420.1, R407.2, Y401.3
unnamed: R403.2, U402.60 (QSPI_SS)
unnamed: R406.1, U402.51 (USB_DM)
unnamed: R405.1, U402.52 (USB_DP)

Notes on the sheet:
RP2354 as per the hardware design datasheet and as per the minimal board schematic from https://datasheets.raspberrypi.com/rp2350/Minimal-KiCAD.zip which is also where the 2354 symbol is from
12MHz crystal as per hw design datasheet

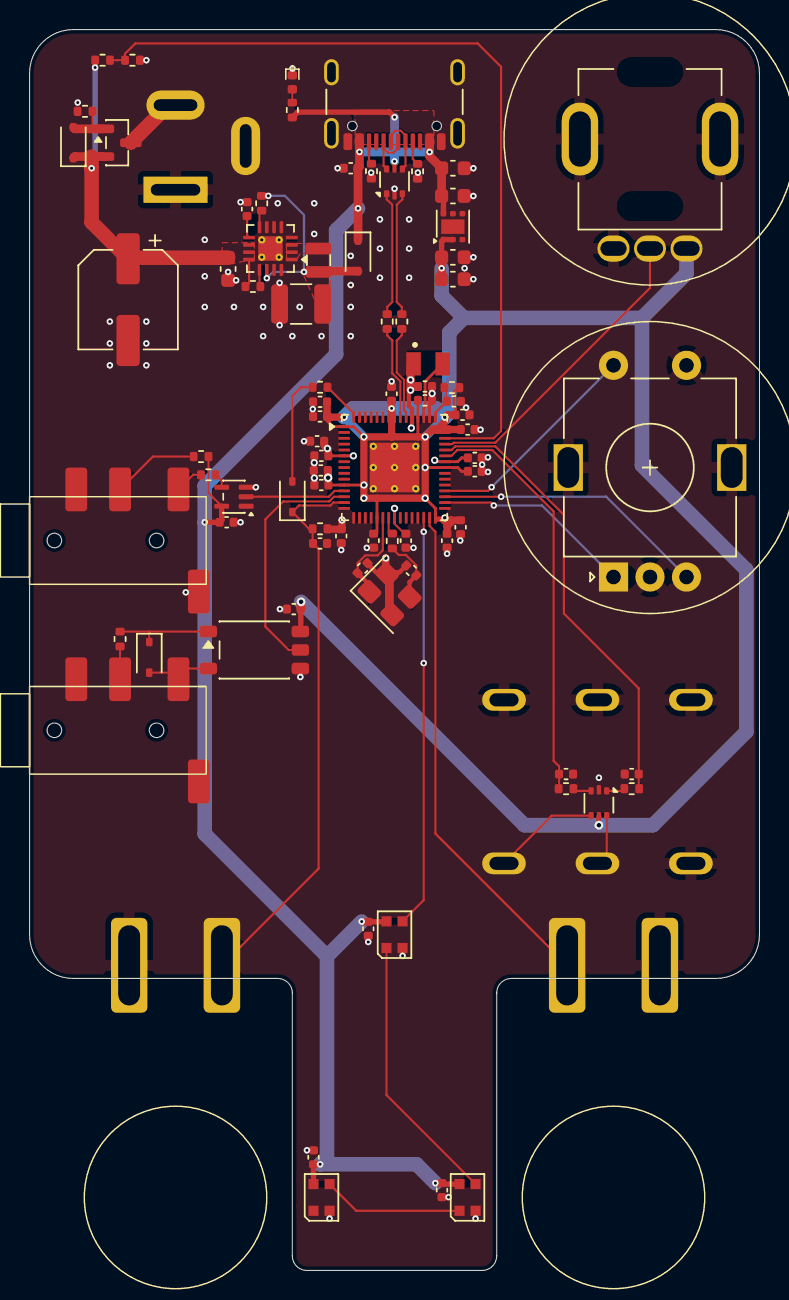
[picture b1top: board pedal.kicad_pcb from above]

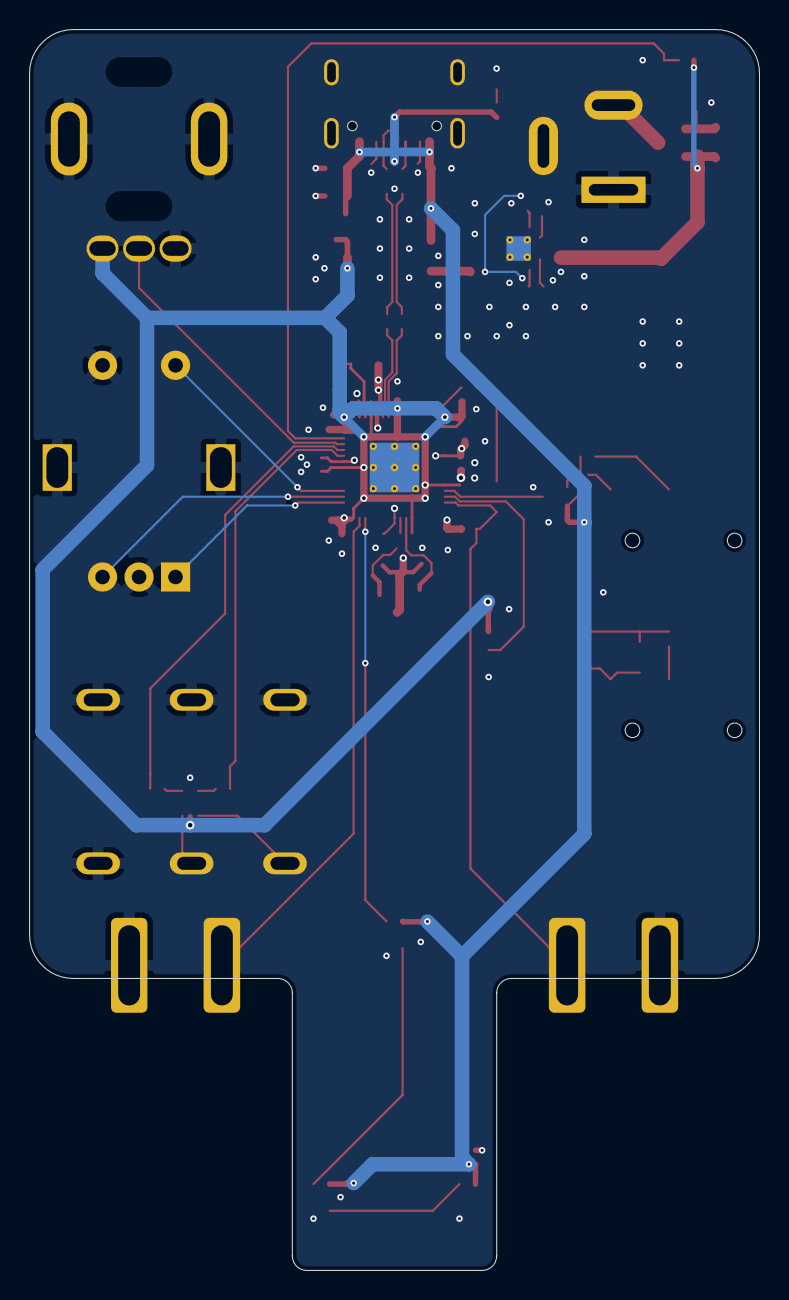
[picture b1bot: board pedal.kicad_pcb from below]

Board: 4 copper layers, 50.0 x 85.0 mm, 85 parts (2 on the bottom side), 52 nets.
